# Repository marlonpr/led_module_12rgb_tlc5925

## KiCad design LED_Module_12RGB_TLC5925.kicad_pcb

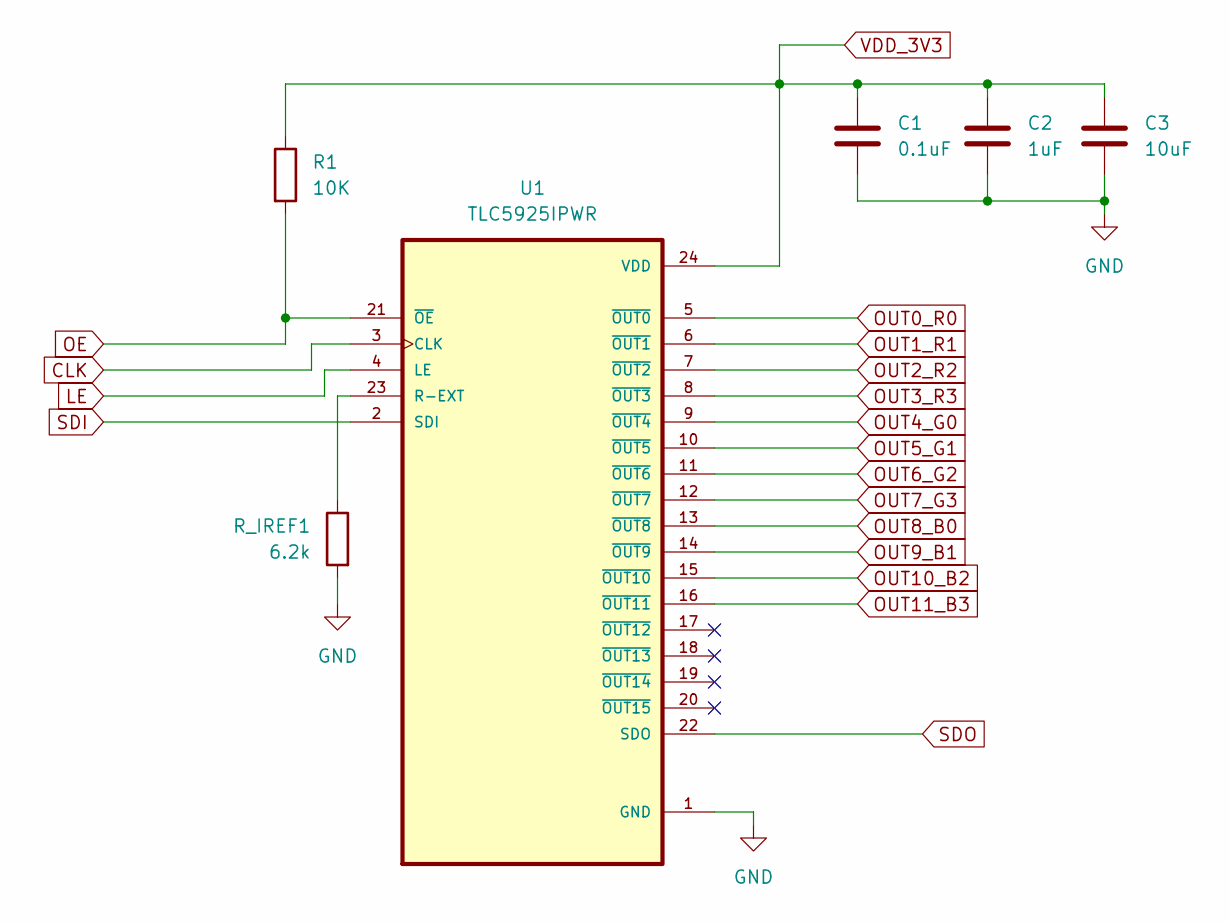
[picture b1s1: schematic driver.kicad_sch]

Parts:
C1: 0.1uF; C_0603_1608Metric_Pad1.08x0.95mm_HandSolder
C2: 1uF; C_1206_3216Metric_Pad1.33x1.80mm_HandSolder
C3: 10uF; C_0805_2012Metric_Pad1.18x1.45mm_HandSolder
R1: 10K; R_1206_3216Metric_Pad1.30x1.75mm_HandSolder
R_IREF1: 6.2k; R_1206_3216Metric_Pad1.30x1.75mm_HandSolder
U1: TLC5925IPWR; SOP65P640X120-24N

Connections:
CLK: U1.3 (CLK); also elsewhere on the board
GND: C1.2, C2.2, C3.2, R_IREF1.2, U1.1 (GND); also elsewhere on the board
LE: U1.4 (LE); also elsewhere on the board
unnamed: R_IREF1.1, U1.23 (R-EXT)
OE: R1.2, U1.21 (~OE); also elsewhere on the board
OUT0_R0: U1.5 (~OUT0); also elsewhere on the board
OUT1_R1: U1.6 (~OUT1); also elsewhere on the board
OUT2_R2: U1.7 (~OUT2); also elsewhere on the board
OUT3_R3: U1.8 (~OUT3); also elsewhere on the board
OUT4_G0: U1.9 (~OUT4); also elsewhere on the board
OUT5_G1: U1.10 (~OUT5); also elsewhere on the board
OUT6_G2: U1.11 (~OUT6); also elsewhere on the board
OUT7_G3: U1.12 (~OUT7); also elsewhere on the board
OUT8_B0: U1.13 (~OUT8); also elsewhere on the board
OUT9_B1: U1.14 (~OUT9); also elsewhere on the board
OUT10_B2: U1.15 (~OUT10); also elsewhere on the board
OUT11_B3: U1.16 (~OUT11); also elsewhere on the board
SDI: U1.2 (SDI); also elsewhere on the board
SDO: U1.22 (SDO); also elsewhere on the board
VDD_3V3: C1.1, C2.1, C3.1, R1.1, U1.24 (VDD); also elsewhere on the board

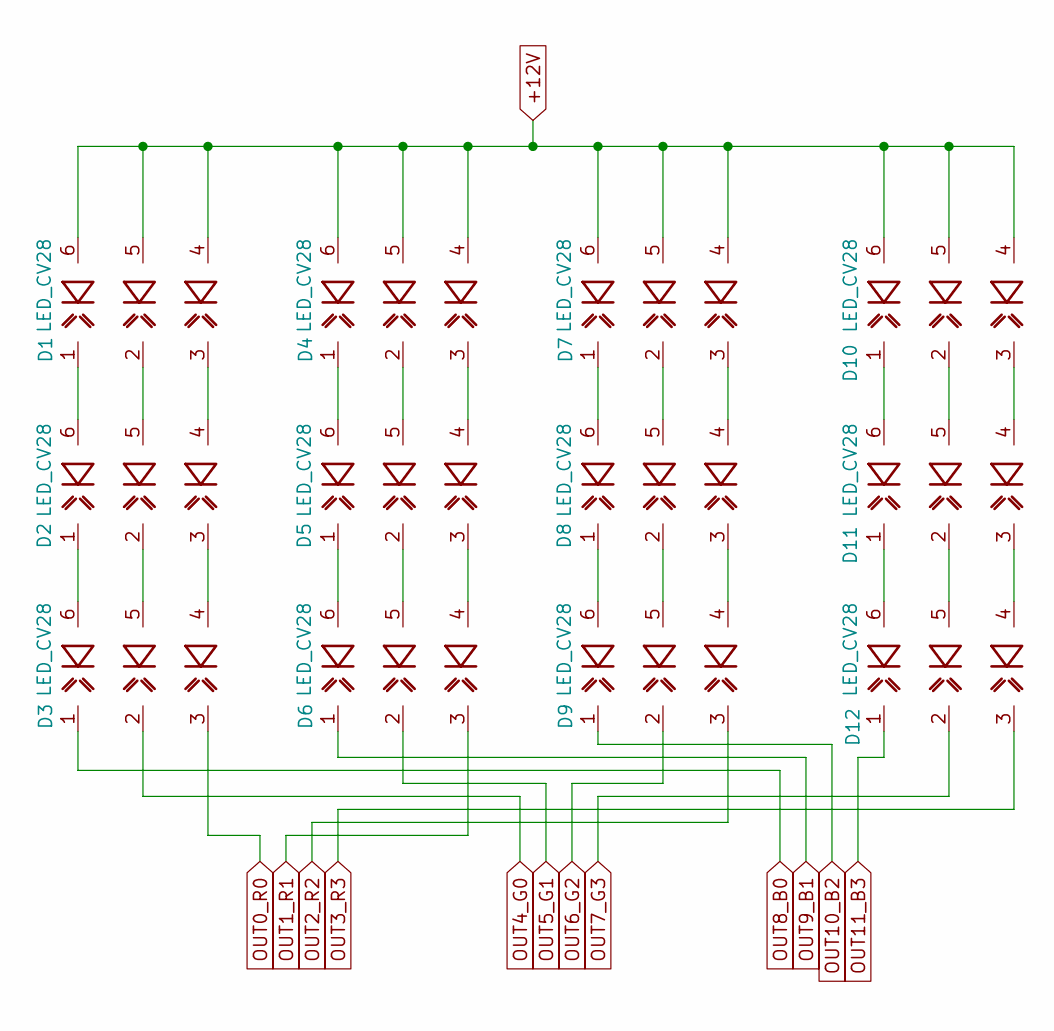
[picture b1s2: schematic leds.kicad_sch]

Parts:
D1, D2, D3, D4, D5, D6, D7, D8, D9, D10, D11, D12: LED_CV28

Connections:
+12V: D1.4 (R_A), D1.5 (G_A), D1.6 (B_A), D4.4 (R_A), D4.5 (G_A), D4.6 (B_A), D7.4 (R_A), D7.5 (G_A), D7.6 (B_A), D10.4 (R_A), D10.5 (G_A), D10.6 (B_A); also elsewhere on the board
unnamed: D1.1 (B_C), D2.6 (B_A)
unnamed: D1.2 (G_C), D2.5 (G_A)
unnamed: D1.3 (R_C), D2.4 (R_A)
unnamed: D2.1 (B_C), D3.6 (B_A)
unnamed: D2.2 (G_C), D3.5 (G_A)
unnamed: D2.3 (R_C), D3.4 (R_A)
unnamed: D4.1 (B_C), D5.6 (B_A)
unnamed: D4.2 (G_C), D5.5 (G_A)
unnamed: D4.3 (R_C), D5.4 (R_A)
unnamed: D5.1 (B_C), D6.6 (B_A)
unnamed: D5.2 (G_C), D6.5 (G_A)
unnamed: D5.3 (R_C), D6.4 (R_A)
unnamed: D7.1 (B_C), D8.6 (B_A)
unnamed: D7.2 (G_C), D8.5 (G_A)
unnamed: D7.3 (R_C), D8.4 (R_A)
unnamed: D8.1 (B_C), D9.6 (B_A)
unnamed: D8.2 (G_C), D9.5 (G_A)
unnamed: D8.3 (R_C), D9.4 (R_A)
unnamed: D10.1 (B_C), D11.6 (B_A)
unnamed: D10.2 (G_C), D11.5 (G_A)
unnamed: D10.3 (R_C), D11.4 (R_A)
unnamed: D11.1 (B_C), D12.6 (B_A)
unnamed: D11.2 (G_C), D12.5 (G_A)
unnamed: D11.3 (R_C), D12.4 (R_A)
OUT0_R0: D3.3 (R_C); also elsewhere on the board
OUT1_R1: D6.3 (R_C); also elsewhere on the board
OUT2_R2: D9.3 (R_C); also elsewhere on the board
OUT3_R3: D12.3 (R_C); also elsewhere on the board
OUT4_G0: D3.2 (G_C); also elsewhere on the board
OUT5_G1: D6.2 (G_C); also elsewhere on the board
OUT6_G2: D9.2 (G_C); also elsewhere on the board
OUT7_G3: D12.2 (G_C); also elsewhere on the board
OUT8_B0: D3.1 (B_C); also elsewhere on the board
OUT9_B1: D6.1 (B_C); also elsewhere on the board
OUT10_B2: D9.1 (B_C); also elsewhere on the board
OUT11_B3: D12.1 (B_C); also elsewhere on the board

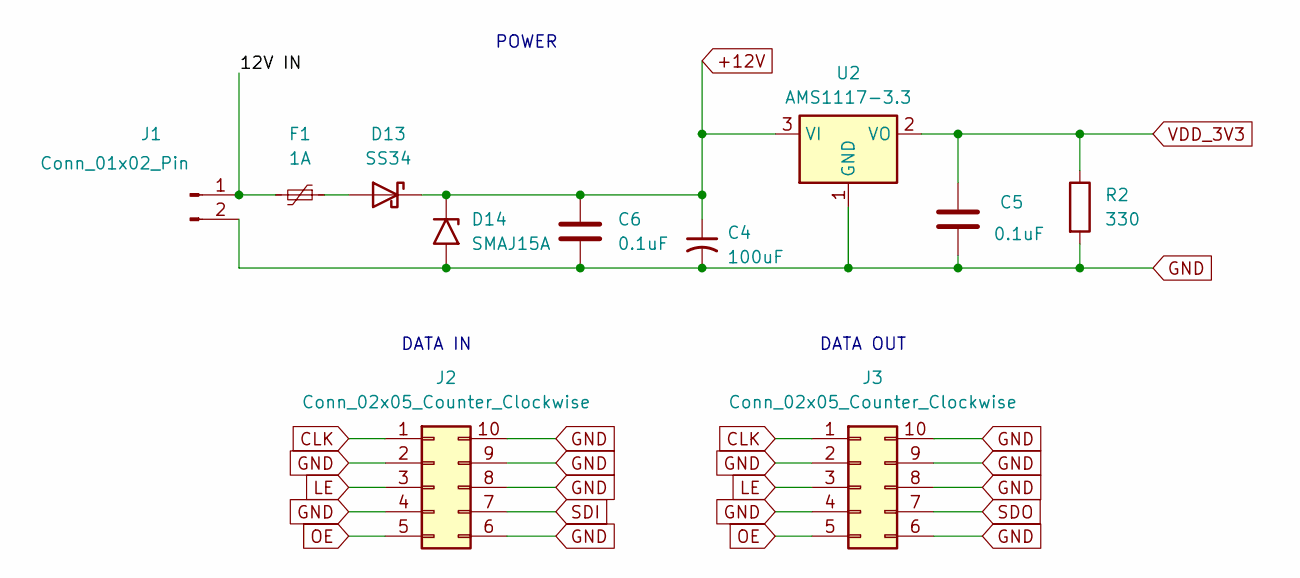
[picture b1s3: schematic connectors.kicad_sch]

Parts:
C4: 100uF; CP_Radial_D5.0mm_P2.50mm
C5, C6: 0.1uF; C_0603_1608Metric_Pad1.08x0.95mm_HandSolder
D13: SS34; D_SMA
D14: SMAJ15A; D_SMA
F1: 1A; R_0603_1608Metric_Pad0.98x0.95mm_HandSolder
J1: Conn_01x02_Pin; PinHeader_1x02_P2.54mm_Vertical
J2, J3: Conn_02x05_Counter_Clockwise; IDC-Header_2x05_P2.54mm_Vertical
R2: 330; R_1206_3216Metric_Pad1.30x1.75mm_HandSolder
U2: AMS1117-3.3; SOT-223-3_TabPin2

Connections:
+12V: C4.1, C6.1, D13.1 (K), D14.1 (A1), U2.3 (VI); also elsewhere on the board
/Connectors/12V IN: F1.2, J1.1
CLK: J2.1, J3.1; also elsewhere on the board
GND: C4.2, C5.1, C6.2, D14.2 (A2), J1.2, J2.2, J2.4, J2.6, J2.8, J2.9, J2.10, J3.2, J3.4, J3.6, J3.8, J3.9, J3.10, R2.2, U2.1 (GND); also elsewhere on the board
LE: J2.3, J3.3; also elsewhere on the board
unnamed: D13.2 (A), F1.1
OE: J2.5, J3.5; also elsewhere on the board
SDI: J2.7; also elsewhere on the board
SDO: J3.7; also elsewhere on the board
VDD_3V3: C5.2, R2.1, U2.2 (VO); also elsewhere on the board

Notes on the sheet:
POWER
DATA IN
DATA OUT

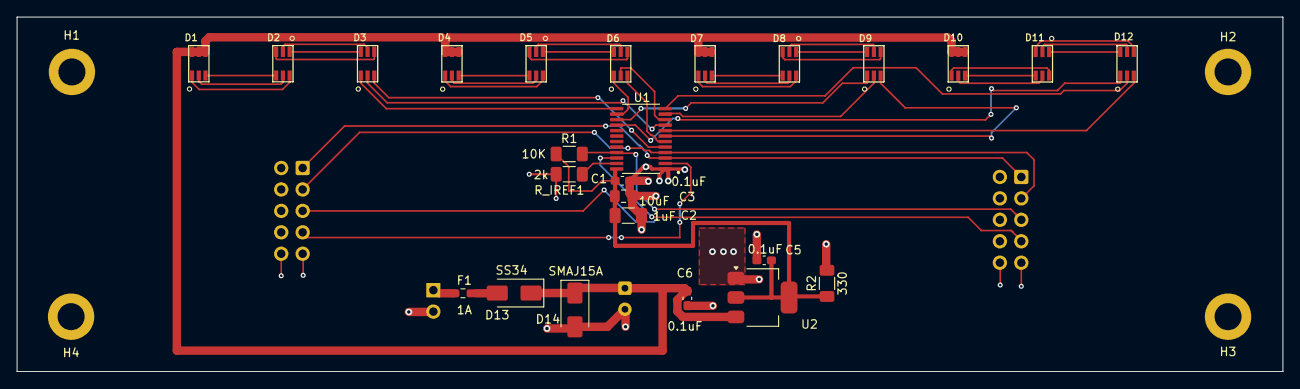
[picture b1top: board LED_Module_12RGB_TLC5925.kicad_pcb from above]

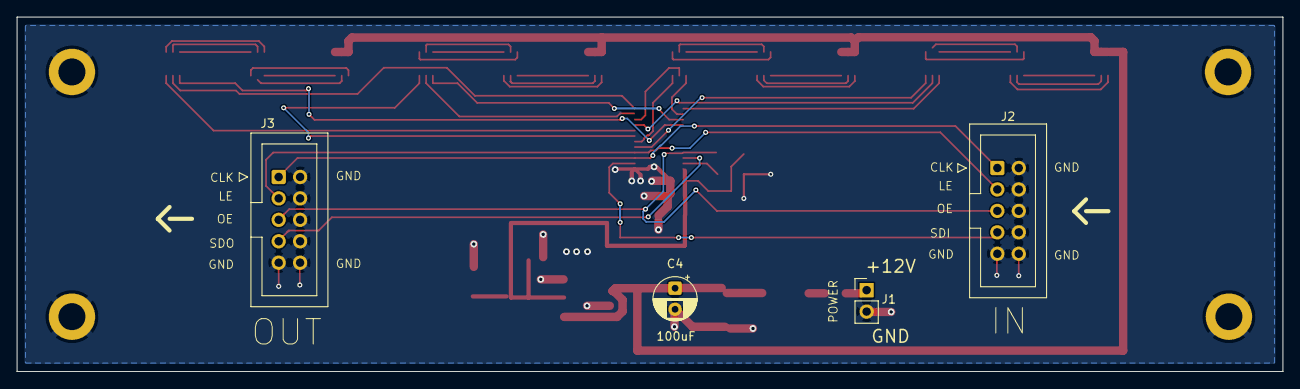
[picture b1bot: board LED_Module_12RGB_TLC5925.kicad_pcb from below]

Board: 2 copper layers, 150.0 x 42.0 mm, 33 parts (4 on the bottom side), 47 nets.

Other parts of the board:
H1, H2, H3, H4: 3.2mm_M3; 3.2mm_M3_TH

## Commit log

2026-04-20 first commit git ignore added
2026-04-20 v0 restored path
2026-04-20 Remove accidental submodule (.history)
2026-04-20 kicad update version
2026-04-22 Place the 12 LEDs in one straight line at 10 mm pitch.
2026-04-23 v0 2 layer needs grounding islands
2026-04-28 v1 ok
2026-05-05 LEDs P10 distance fix
2026-05-05 3D models added
2026-05-06 improved trace size and vias
2026-05-06 cleanup tracks and vias
2026-05-20 gitignore Mac folder
